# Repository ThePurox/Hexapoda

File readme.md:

# Hexapoda
The Hexapoda is a [hummingbird](https://github.com/PJE66/hummingbird) style 30 key keyboard designed around [hexagonal keycaps](https://hw.s-ol.nu/HEX-keycaps/), which require Choc v1 switches.
It uses the CH552T controller and [FAK firmware](https://github.com/semickolon/fak).

The electronic design is inspired by the [MIAO MCU board](https://github.com/kilipan/miao).

# Buildguide
Soldering should be straight forward with the help of the [interactive bill of materials](bom/ibom.html)
The orientation of `U1` and `U2` are indicated by small arrows on the PCB.
The orientaion `D16` is such that its white line is on the side where the footprint on the silkscreen also has a white line.
For all other components, the orientation does not matter, or their form-factor allows only one orientation (`D1-D15`).
Make sure to also solder the metal legs on the side, as they will give stability to the jack.
Do **not** plug in a USB-cabel without soldering the metal legs on the side of the USB-jack! You will most likely rip off the USB-jack when unplugging the USB-cable!

# Flashing firmware
This keyboard is designed for the [FAK-firmware](https://github.com/semickolon/fak).
I've provided some example configuration files in [my fork](https://github.com/ThePurox/fak-config) of the fak-config repository with the keyboard name `hexapoda`.
The push-button closer to the USB-jack is the `BOOT` button. The one closer to the thumb keys is the `RESET` button.

# BOM
| Part             | LCSC-Part Nr | amount |
|------------------|--------------|--------|
| USB-C            | C2765186     | 1      |
| CH552T           | C111367      | 1      |
| BAV70 Diodes     | C727123      | 15     |
| USBLC6-2SC6      | C6807798     | 1      |
| PMEG2010EA       | C193668      | 1      |
| Push buttons     | C115357      | 2      |
| Fuse             | C311055      | 1      |
| 5.1k-Resistor    | C23186       | 2      |
| 10k-Resistor     | C25804       | 1      |
| 1uF-Capacitor    | C2991434     | 2      |
| Hot-Swap-Sockets |              | 30     |
| Choc V1 Switches |              | 30     |

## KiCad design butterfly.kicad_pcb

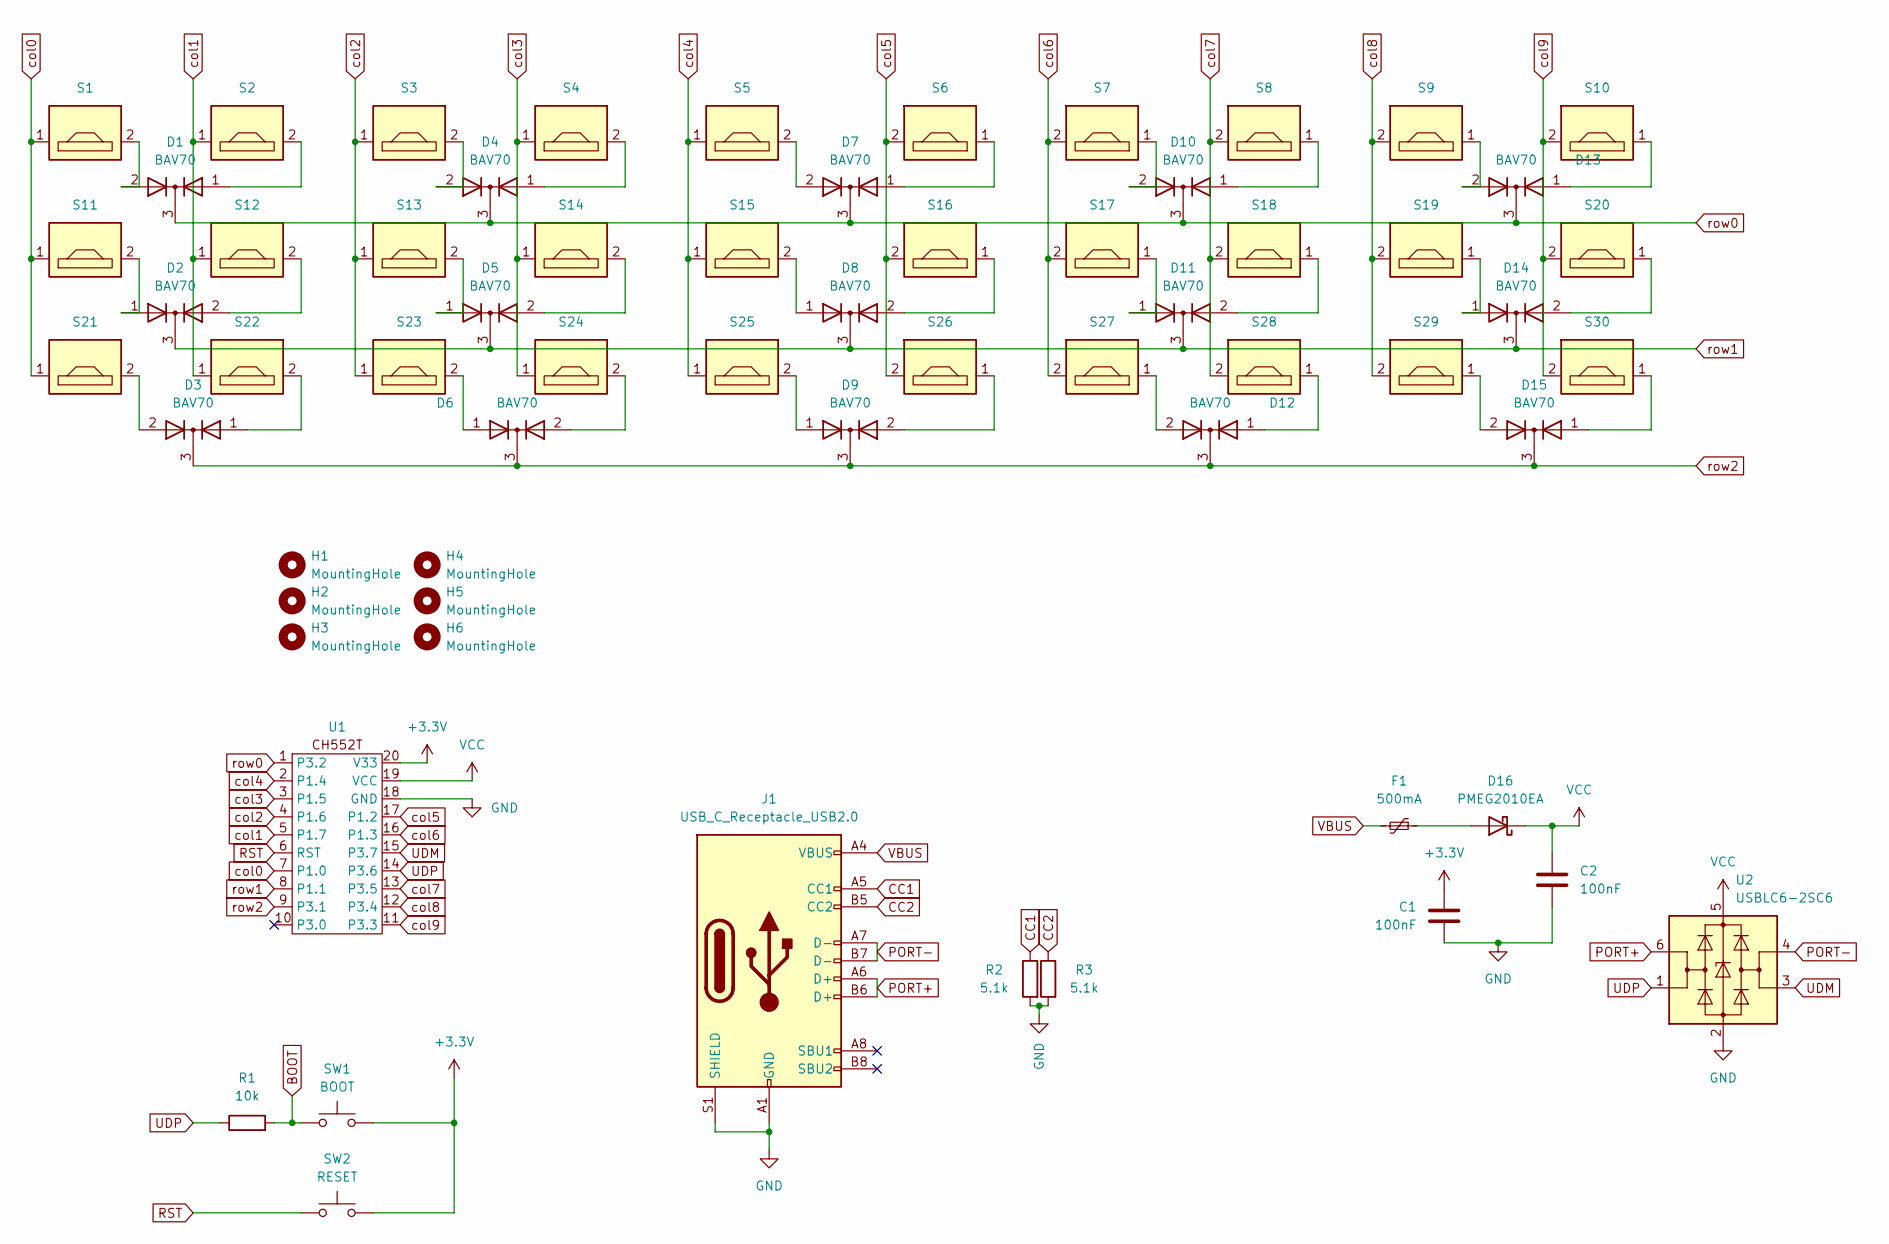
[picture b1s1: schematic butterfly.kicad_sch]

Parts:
C1, C2: 100nF; C_0603_1608Metric_Pad1.08x0.95mm_HandSolder
D1, D2, D3, D4, D5, D6, D7, D8, D9, D10, D11, D12, D13, D14, D15: BAV70; SOT-23
D16: PMEG2010EA; D_SOD-323_HandSoldering
F1: 500mA; Fuse_0603_1608Metric_Pad1.05x0.95mm_HandSolder
H1, H2, H3, H4, H5, H6: MountingHole; MountingHole_2.2mm_M2
J1: USB_C_Receptacle_USB2.0; USB_C_Receptacle_HRO_TYPE-C-31-M-12
R1: 10k; R_0603_1608Metric_Pad0.98x0.95mm_HandSolder
R2, R3: 5.1k; R_0603_1608Metric_Pad0.98x0.95mm_HandSolder
S1, S2, S3, S4, S5, S6, S7, S8, S9, S10, S11, S12, S13, S14, S15, S16, S17, S18, S19, S20, S21, S22, S23, S24, S25, S26, S27, S28, S29, S30: PG1350; PG1350_hotswap
SW1: BOOT; SW_Push_SPST_NO_Alps_SKRK
SW2: RESET; SW_Push_SPST_NO_Alps_SKRK
U1: TSSOP-20_4.4x6.5mm_P0.65mm
U2: USBLC6-2SC6; SOT-23-6

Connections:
+3.3V: C1.1, SW1.2, SW2.2, U1.20 (V33)
BOOT: R1.2, SW1.1
CC1: J1.A5 (CC1), R2.1
CC2: J1.B5 (CC2), R3.1
GND: C1.2, C2.2, J1.A1 (GND), J1.A12 (GND), J1.B1 (GND), J1.B12 (GND), J1.S1 (SHIELD), R2.2, R3.2, U1.18 (GND), U2.2 (GND)
unnamed: D1.1 (A), S2.2
unnamed: D1.2 (A), S1.2
unnamed: D2.1 (A), S11.2
unnamed: D2.2 (A), S12.2
unnamed: D3.1 (A), S22.2
unnamed: D3.2 (A), S21.2
unnamed: D4.1 (A), S4.2
unnamed: D4.2 (A), S3.2
unnamed: D5.1 (A), S13.2
unnamed: D5.2 (A), S14.2
unnamed: D6.1 (A), S23.2
unnamed: D6.2 (A), S24.2
unnamed: D7.1 (A), S6.1
unnamed: D7.2 (A), S5.2
unnamed: D8.1 (A), S15.2
unnamed: D8.2 (A), S16.1
unnamed: D9.1 (A), S25.2
unnamed: D9.2 (A), S26.1
unnamed: D10.1 (A), S8.1
unnamed: D10.2 (A), S7.1
unnamed: D11.1 (A), S17.1
unnamed: D11.2 (A), S18.1
unnamed: D12.1 (A), S28.1
unnamed: D12.2 (A), S27.1
unnamed: D13.1 (A), S10.1
unnamed: D13.2 (A), S9.1
unnamed: D14.1 (A), S19.1
unnamed: D14.2 (A), S20.1
unnamed: D15.1 (A), S30.1
unnamed: D15.2 (A), S29.1
unnamed: D16.2 (A), F1.1
PORT+: J1.A6 (D+), J1.B6 (D+), U2.6 (I/O1)
PORT-: J1.A7 (D-), J1.B7 (D-), U2.4 (I/O2)
RST: SW2.1, U1.6 (RST)
UDM: U1.15 (P3.7), U2.3 (I/O2)
UDP: R1.1, U1.14 (P3.6), U2.1 (I/O1)
VBUS: F1.2, J1.A4 (VBUS), J1.A9 (VBUS), J1.B4 (VBUS), J1.B9 (VBUS)
VCC: C2.1, D16.1 (K), U1.19 (VCC), U2.5 (VBUS)
col0: S1.1, S11.1, S21.1, U1.7 (P1.0)
col1: S2.1, S12.1, S22.1, U1.5 (P1.7)
col2: S3.1, S13.1, S23.1, U1.4 (P1.6)
col3: S4.1, S14.1, S24.1, U1.3 (P1.5)
col4: S5.1, S15.1, S25.1, U1.2 (P1.4)
col5: S6.2, S16.2, S26.2, U1.17 (P1.2)
col6: S7.2, S17.2, S27.2, U1.16 (P1.3)
col7: S8.2, S18.2, S28.2, U1.13 (P3.5)
col8: S9.2, S19.2, S29.2, U1.12 (P3.4)
col9: S10.2, S20.2, S30.2, U1.11 (P3.3)
row0: D1.3 (K), D4.3 (K), D7.3 (K), D10.3 (K), D13.3 (K), U1.1 (P3.2)
row1: D2.3 (K), D5.3 (K), D8.3 (K), D11.3 (K), D14.3 (K), U1.8 (P1.1)
row2: D3.3 (K), D6.3 (K), D9.3 (K), D12.3 (K), D15.3 (K), U1.9 (P3.1)

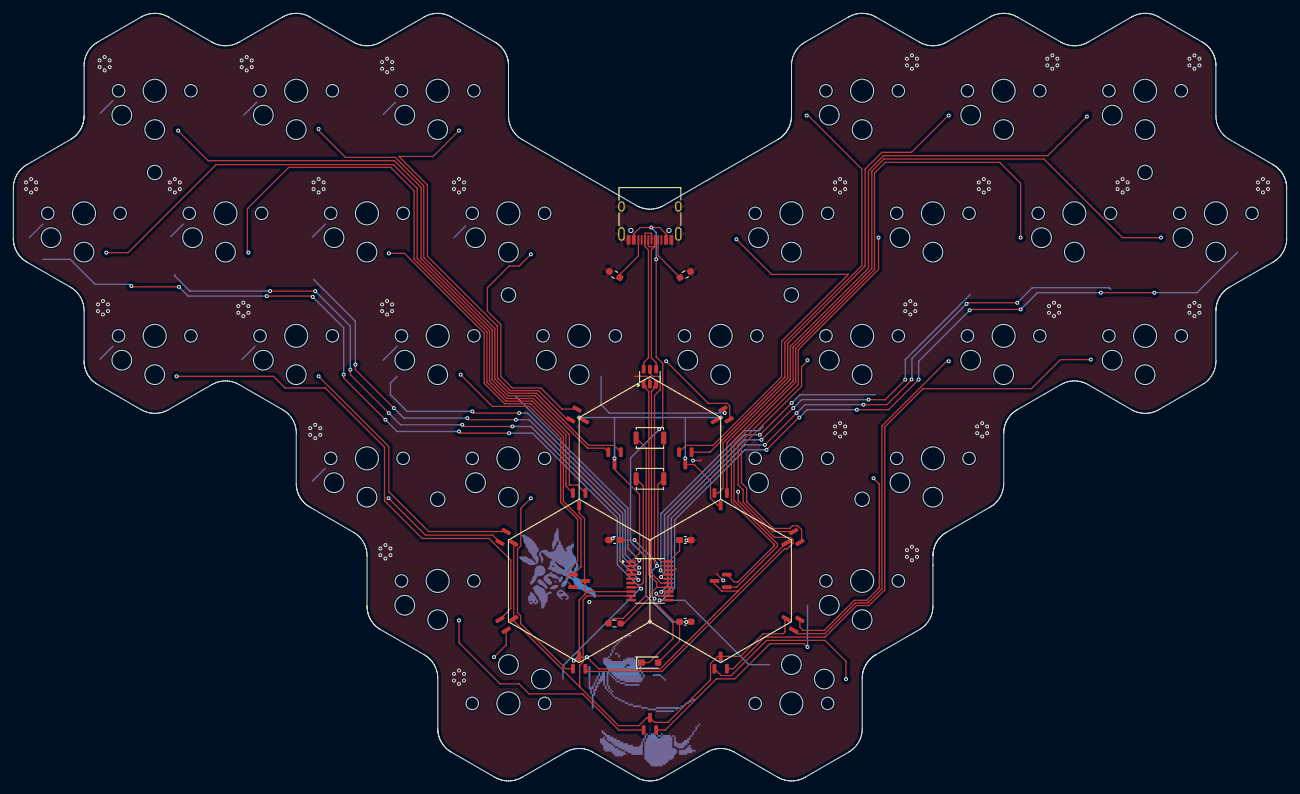
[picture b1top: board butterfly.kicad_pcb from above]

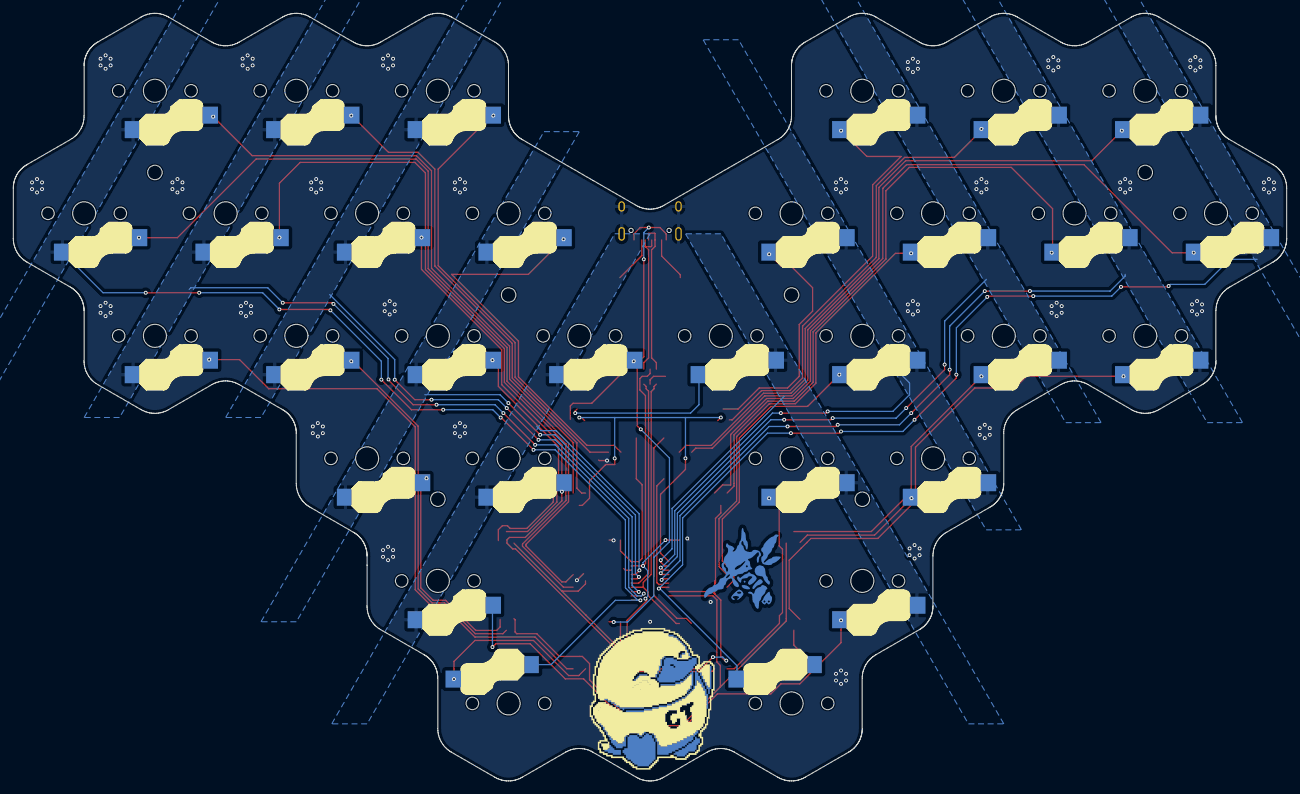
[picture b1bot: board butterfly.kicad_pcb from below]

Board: 2 copper layers, 193.5 x 116.6 mm, 63 parts (30 on the bottom side), 56 nets.

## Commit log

2024-05-23 init
2024-05-24 before ground-hexing
2024-05-25 hex-hex
2024-06-04 added readme
2024-06-07 added real pictures
2024-06-23 added ibom
2024-06-23 added buildguide
2024-06-23 added BOM
2024-06-25 added more explicit warning about soldering the USB-jack mechanically
2024-06-25 added description of buttons
2024-10-08 added credits
2024-11-27 added case
